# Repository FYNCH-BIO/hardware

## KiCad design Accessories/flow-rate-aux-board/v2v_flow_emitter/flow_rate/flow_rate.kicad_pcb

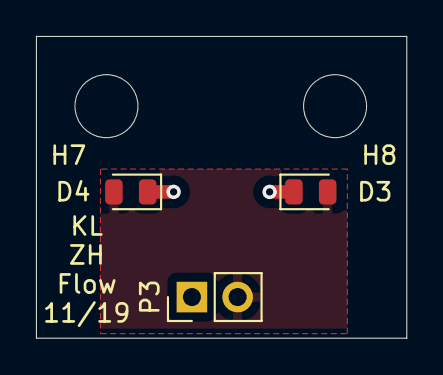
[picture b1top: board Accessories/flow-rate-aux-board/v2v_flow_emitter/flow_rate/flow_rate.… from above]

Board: 2 copper layers, 20.6 x 16.8 mm, 5 parts (0 on the bottom side), 2 nets.

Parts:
D3, D4: D; D_0805_2012Metric
H7, H8: MountingHole; MountingHole_3.5mm
P3: CONN_01X02; PinHeader_1x02_P2.54mm_Vertical

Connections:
/LED_GND: D3.1, D4.1, P3.1
/LED_PWR: D3.2, D4.2, P3.2

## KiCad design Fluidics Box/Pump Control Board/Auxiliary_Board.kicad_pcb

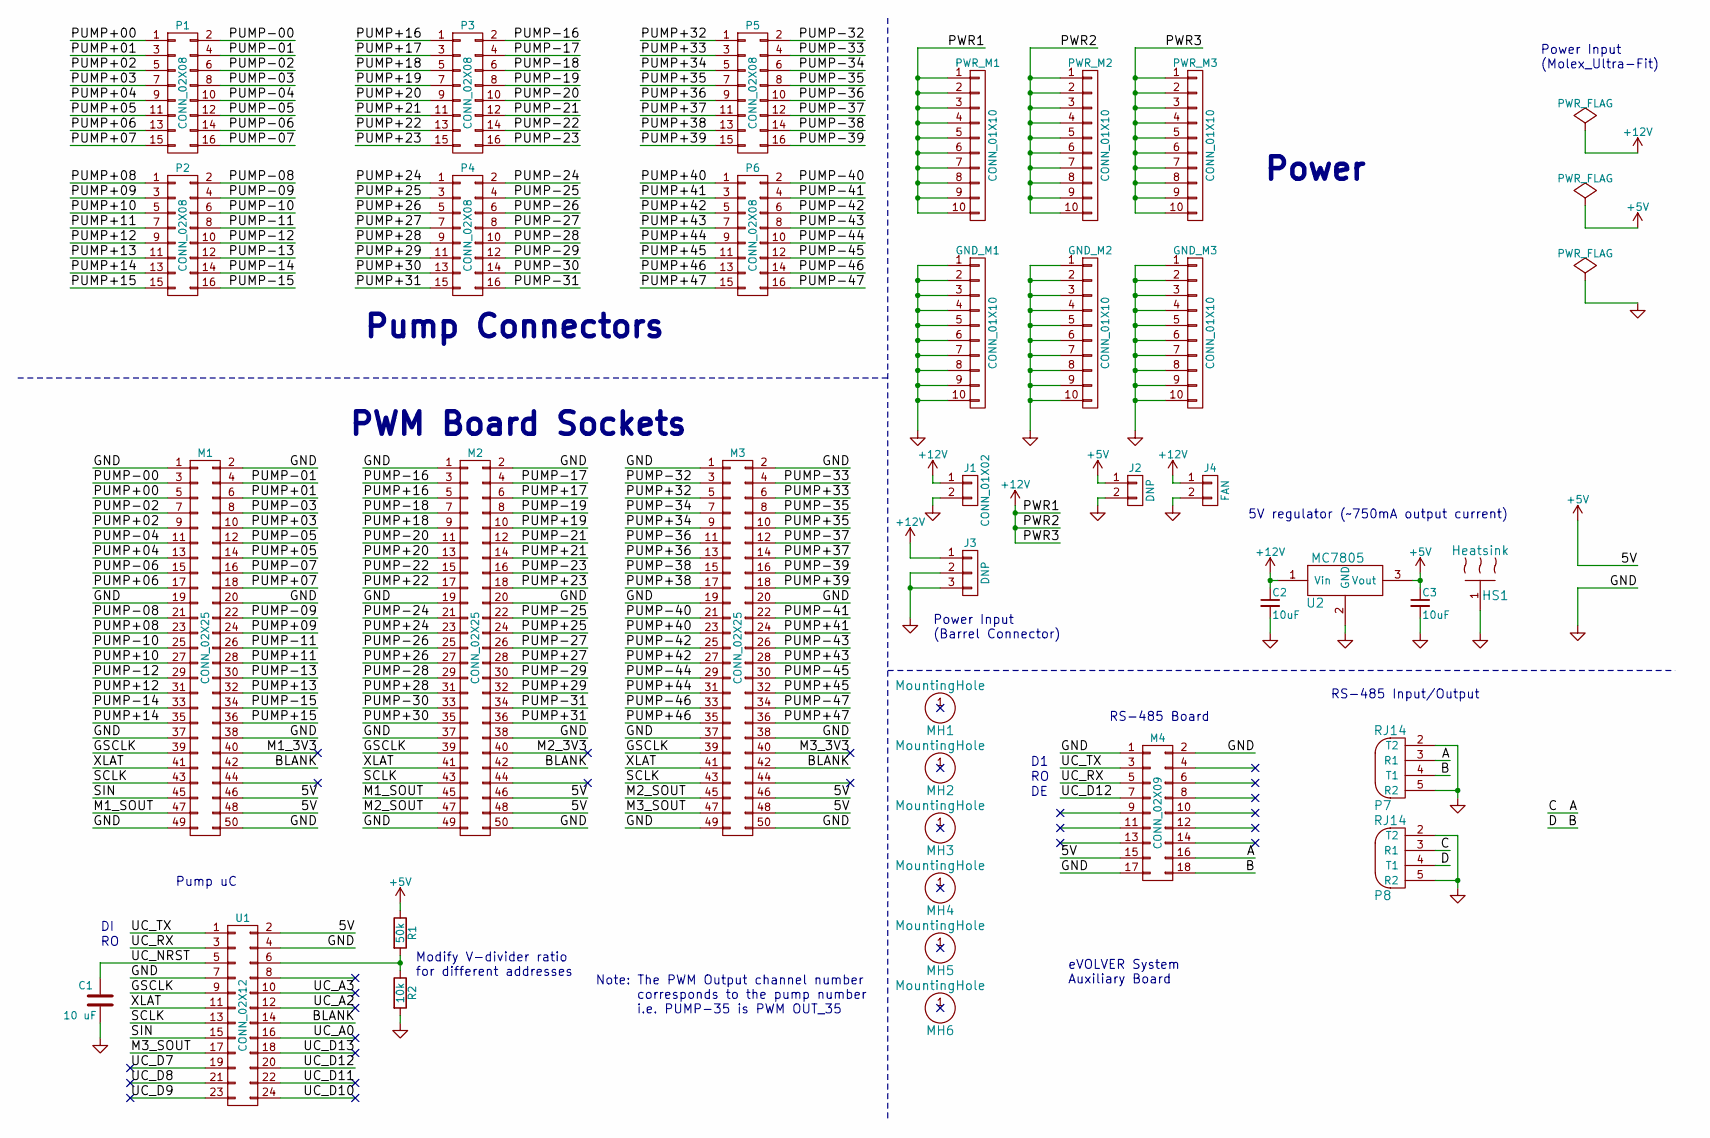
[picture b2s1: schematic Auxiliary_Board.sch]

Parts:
C1: 10 uF; FK18X5R0J105K
C2, C3: 10uF; FK18X5R0J105K
GND_M1, GND_M2, GND_M3: CONN_01X10; 10pin_tenth_in
HS1: Heatsink; CSM222-30AE
J1: CONN_01X02; OSTYK51102030
J2: DNP; OSTYK51102030
J3: DNP; 2.1mm_DC_Jack
J4: FAN; OSTYK51102030
M1, M2, M3: CONN_02X25; 50_pin_10in
M4: CONN_02X09; 2x_9_pin_10in
MH1, MH2, MH3, MH4, MH5, MH6: MountingHole; mh_632
P1, P2, P3, P4, P5, P6: CONN_02X08; 2x8_conn_10in
P7, P8: RJ14
PWR_M1, PWR_M2, PWR_M3: CONN_01X10; 10pin_tenth_in
R1: 50k; R_0.25W
R2: 10k; R_0.25W
U1: CONN_02X12; 24_pin_10in
U2: MC7805; TO-220

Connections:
+5V: C3.1, J2.1, M1.46, M1.48, M2.46, M2.48, M3.46, M3.48, M4.15, R1.1, U1.2, U2.3 (Vout)
+12V: C2.1, J1.1, J3.1, J4.1, PWR_M1.1, PWR_M1.2, PWR_M1.3, PWR_M1.4, PWR_M1.5, PWR_M1.6, PWR_M1.7, PWR_M1.8, PWR_M1.9, PWR_M1.10, PWR_M2.1, PWR_M2.2, PWR_M2.3, PWR_M2.4, PWR_M2.5, PWR_M2.6, PWR_M2.7, PWR_M2.8, PWR_M2.9, PWR_M2.10, PWR_M3.1, PWR_M3.2, PWR_M3.3, PWR_M3.4, PWR_M3.5, PWR_M3.6, PWR_M3.7, PWR_M3.8, PWR_M3.9, PWR_M3.10, U2.1 (Vin)
/A: M4.16, P7.3 (R1), P8.3 (R1)
/B: M4.18, P7.4 (T1), P8.4 (T1)
/BLANK: M1.42, M2.42, M3.42, U1.14
/GSCLK: M1.39, M2.39, M3.39, U1.9
/M1_3V3: M1.40
/M1_SOUT: M1.47, M2.45
/M2_3V3: M2.40
/M2_SOUT: M2.47, M3.45
/M3_3V3: M3.40
/M3_SOUT: M3.47, U1.17
/PUMP+00: M1.5, P1.1
/PUMP+01: M1.6, P1.3
/PUMP+02: M1.9, P1.5
/PUMP+03: M1.10, P1.7
/PUMP+04: M1.13, P1.9
/PUMP+05: M1.14, P1.11
/PUMP+06: M1.17, P1.13
/PUMP+07: M1.18, P1.15
/PUMP+08: M1.23, P2.1
/PUMP+09: M1.24, P2.3
/PUMP+10: M1.27, P2.5
/PUMP+11: M1.28, P2.7
/PUMP+12: M1.31, P2.9
/PUMP+13: M1.32, P2.11
/PUMP+14: M1.35, P2.13
/PUMP+15: M1.36, P2.15
/PUMP+16: M2.5, P3.1
/PUMP+17: M2.6, P3.3
/PUMP+18: M2.9, P3.5
/PUMP+19: M2.10, P3.7
/PUMP+20: M2.13, P3.9
/PUMP+21: M2.14, P3.11
/PUMP+22: M2.17, P3.13
/PUMP+23: M2.18, P3.15
/PUMP+24: M2.23, P4.1
/PUMP+25: M2.24, P4.3
/PUMP+26: M2.27, P4.5
/PUMP+27: M2.28, P4.7
/PUMP+28: M2.31, P4.9
/PUMP+29: M2.32, P4.11
/PUMP+30: M2.35, P4.13
/PUMP+31: M2.36, P4.15
/PUMP+32: M3.5, P5.1
/PUMP+33: M3.6, P5.3
/PUMP+34: M3.9, P5.5
/PUMP+35: M3.10, P5.7
/PUMP+36: M3.13, P5.9
/PUMP+37: M3.14, P5.11
/PUMP+38: M3.17, P5.13
/PUMP+39: M3.18, P5.15
/PUMP+40: M3.23, P6.1
/PUMP+41: M3.24, P6.3
/PUMP+42: M3.27, P6.5
/PUMP+43: M3.28, P6.7
/PUMP+44: M3.31, P6.9
/PUMP+45: M3.32, P6.11
/PUMP+46: M3.35, P6.13
/PUMP+47: M3.36, P6.15
/PUMP-00: M1.3, P1.2
/PUMP-01: M1.4, P1.4
/PUMP-02: M1.7, P1.6
/PUMP-03: M1.8, P1.8
/PUMP-04: M1.11, P1.10
/PUMP-05: M1.12, P1.12
/PUMP-06: M1.15, P1.14
/PUMP-07: M1.16, P1.16
/PUMP-08: M1.21, P2.2
/PUMP-09: M1.22, P2.4
/PUMP-10: M1.25, P2.6
/PUMP-11: M1.26, P2.8
/PUMP-12: M1.29, P2.10
/PUMP-13: M1.30, P2.12
/PUMP-14: M1.33, P2.14
/PUMP-15: M1.34, P2.16
/PUMP-16: M2.3, P3.2
/PUMP-17: M2.4, P3.4
/PUMP-18: M2.7, P3.6
/PUMP-19: M2.8, P3.8
/PUMP-20: M2.11, P3.10
/PUMP-21: M2.12, P3.12
/PUMP-22: M2.15, P3.14
/PUMP-23: M2.16, P3.16
/PUMP-24: M2.21, P4.2
/PUMP-25: M2.22, P4.4
/PUMP-26: M2.25, P4.6
/PUMP-27: M2.26, P4.8
/PUMP-28: M2.29, P4.10
/PUMP-29: M2.30, P4.12
/PUMP-30: M2.33, P4.14
/PUMP-31: M2.34, P4.16
/PUMP-32: M3.3, P5.2
/PUMP-33: M3.4, P5.4
/PUMP-34: M3.7, P5.6
/PUMP-35: M3.8, P5.8
/PUMP-36: M3.11, P5.10
/PUMP-37: M3.12, P5.12
/PUMP-38: M3.15, P5.14
/PUMP-39: M3.16, P5.16
/PUMP-40: M3.21, P6.2
/PUMP-41: M3.22, P6.4
/PUMP-42: M3.25, P6.6
/PUMP-43: M3.26, P6.8
/PUMP-44: M3.29, P6.10
/PUMP-45: M3.30, P6.12
/PUMP-46: M3.33, P6.14
/PUMP-47: M3.34, P6.16
/SCLK: M1.43, M2.43, M3.43, U1.13
/SIN: M1.45, U1.15
/UC_A0: U1.16
/UC_A2: U1.12
/UC_A3: U1.10
/UC_D7: U1.19
/UC_D8: U1.21
/UC_D9: U1.23
/UC_D10: U1.24
/UC_D11: U1.22
/UC_D12: M4.7, U1.20
/UC_D13: U1.18
/UC_NRST: C1.1, U1.5
/UC_RX: M4.5, U1.3
/UC_TX: M4.3, U1.1
/XLAT: M1.41, M2.41, M3.41, U1.11
GND: C1.2, C2.2, C3.2, GND_M1.1, GND_M1.2, GND_M1.3, GND_M1.4, GND_M1.5, GND_M1.6, GND_M1.7, GND_M1.8, GND_M1.9, GND_M1.10, GND_M2.1, GND_M2.2, GND_M2.3, GND_M2.4, GND_M2.5, GND_M2.6, GND_M2.7, GND_M2.8, GND_M2.9, GND_M2.10, GND_M3.1, GND_M3.2, GND_M3.3, GND_M3.4, GND_M3.5, GND_M3.6, GND_M3.7, GND_M3.8, GND_M3.9, GND_M3.10, HS1.1, J1.2, J2.2, J3.2, J3.3, J4.2, M1.1, M1.2, M1.19, M1.20, M1.37, M1.38, M1.49, M1.50, M2.1, M2.2, M2.19, M2.20, M2.37, M2.38, M2.49, M2.50, M3.1, M3.2, M3.19, M3.20, M3.37, M3.38, M3.49, M3.50, M4.1, M4.2, M4.17, P7.2 (T2), P7.5 (R2), P8.2 (T2), P8.5 (R2), R2.2, U1.4, U1.7, U2.2 (GND)
unnamed: R1.2, R2.1, U1.6

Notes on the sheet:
RS-485 Board
RS-485 Input/Output
Power Input (Barrel Connector)
Power Input (Molex_Ultra-Fit)
Pump uC
Pump Connectors
PWM Board Sockets
Power
Note: The PWM Output channel number corresponds to the pump number i.e. PUMP-35 is PWM OUT_35
eVOLVER System Auxiliary Board
5V regulator (~~750mA output current)
Modify V-divider ratio for different addresses

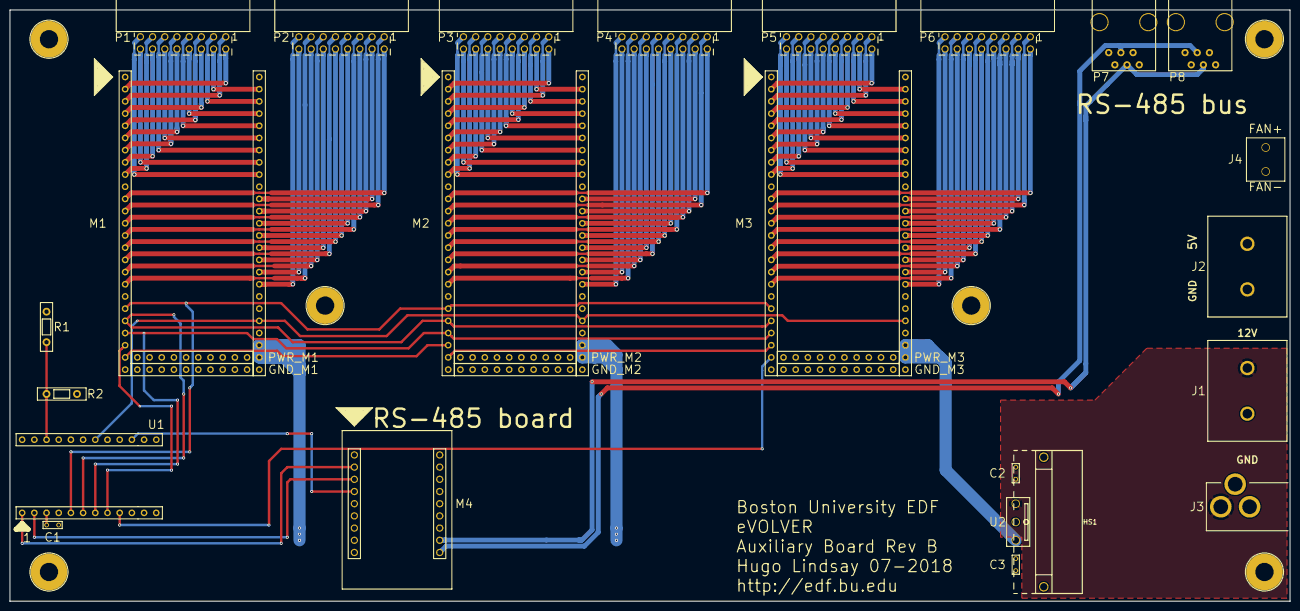
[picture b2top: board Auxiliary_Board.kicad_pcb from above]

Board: 4 copper layers, 266.7 x 123.2 mm, 36 parts (0 on the bottom side), 114 nets.

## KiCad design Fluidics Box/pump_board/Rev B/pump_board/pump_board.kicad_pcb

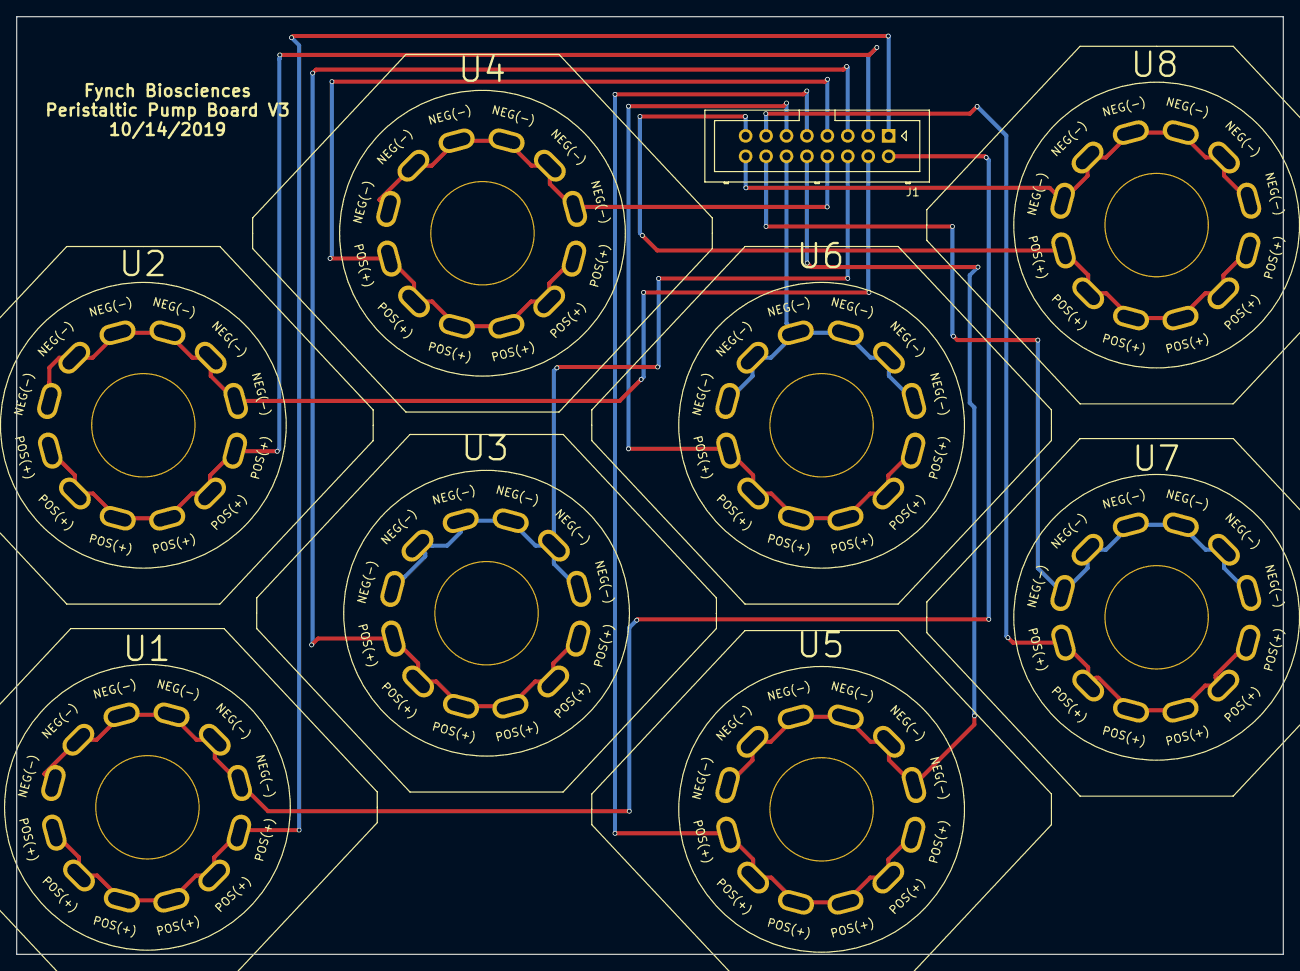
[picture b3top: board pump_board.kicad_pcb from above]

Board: 2 copper layers, 157.5 x 116.6 mm, 9 parts (0 on the bottom side), 16 nets.

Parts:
J1: Conn_02x08_Odd_Even; Multicomp_MC9A12-1634_2x08x2.54mm_Straight
U1, U2, U3, U4, U5, U6, U7, U8: peristaltic_pump; peristlatic_pump_15deg_offset

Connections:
unnamed: J1.1, U1.1
unnamed: J1.2, U1.2
unnamed: J1.3, U2.1
unnamed: J1.4, U2.2
unnamed: J1.5, U3.1
unnamed: J1.6, U3.2
unnamed: J1.7, U4.1
unnamed: J1.8, U4.2
unnamed: J1.9, U5.1
unnamed: J1.10, U5.2
unnamed: J1.11, U6.1
unnamed: J1.12, U6.2
unnamed: J1.13, U7.1
unnamed: J1.14, U7.2
unnamed: J1.15, U8.1
unnamed: J1.16, U8.2

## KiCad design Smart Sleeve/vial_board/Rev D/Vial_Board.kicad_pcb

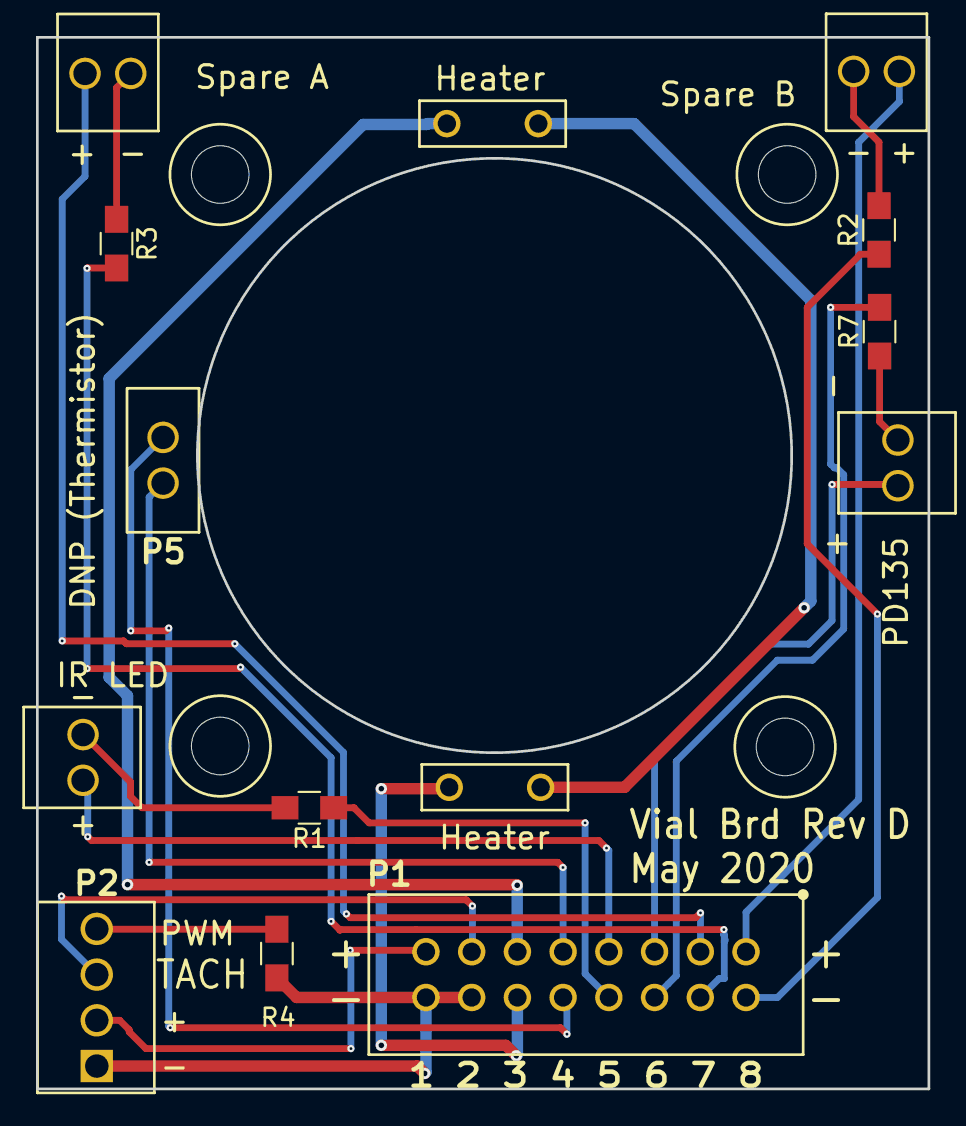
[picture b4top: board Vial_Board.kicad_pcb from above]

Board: 2 copper layers, 49.5 x 58.4 mm, 14 parts (0 on the bottom side), 21 nets.

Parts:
P1: CONN_02X08; 2x8_pin_10in
P2: CONN_01X04; 4_ScrewTerm
P5: DNP (Thermistor); Thermistor
P6: IR LED; screw_terminal
P7: PD135; screw_terminal
P8: Spare B; screw_terminal
P9: Spare A; screw_terminal
R1, R2, R3, R7: 82; R_0805_HandSoldering
R4: R; R_0805_HandSoldering
R5: Heater 1; Heater
R6: Heater 2; Heater

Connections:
/FAN+: P1.15, P2.2
/FAN-: P1.14, P1.16, P2.1, R4.2
/FS+: P1.13, P2.3
/HTR+: P1.11, R5.1
/HTR-: P1.12, R6.2
/LED+: P1.7, P6.1
/LED-: P1.8, R1.1
/PD+: P1.5, P7.1
/PD-: P1.6, R7.2
/PWM: P2.4, R4.1
/SPA+: P1.3, P9.1
/SPA-: P1.4, R3.2
/SPB+: P1.1, P8.1
/SPB-: P1.2, R2.1
/TS+: P1.9, P5.1
/TS-: P1.10, P5.2
unnamed: P6.2, R1.2
unnamed: P7.2, R7.1
unnamed: P8.2, R2.2
unnamed: P9.2, R3.1
unnamed: R5.2, R6.1

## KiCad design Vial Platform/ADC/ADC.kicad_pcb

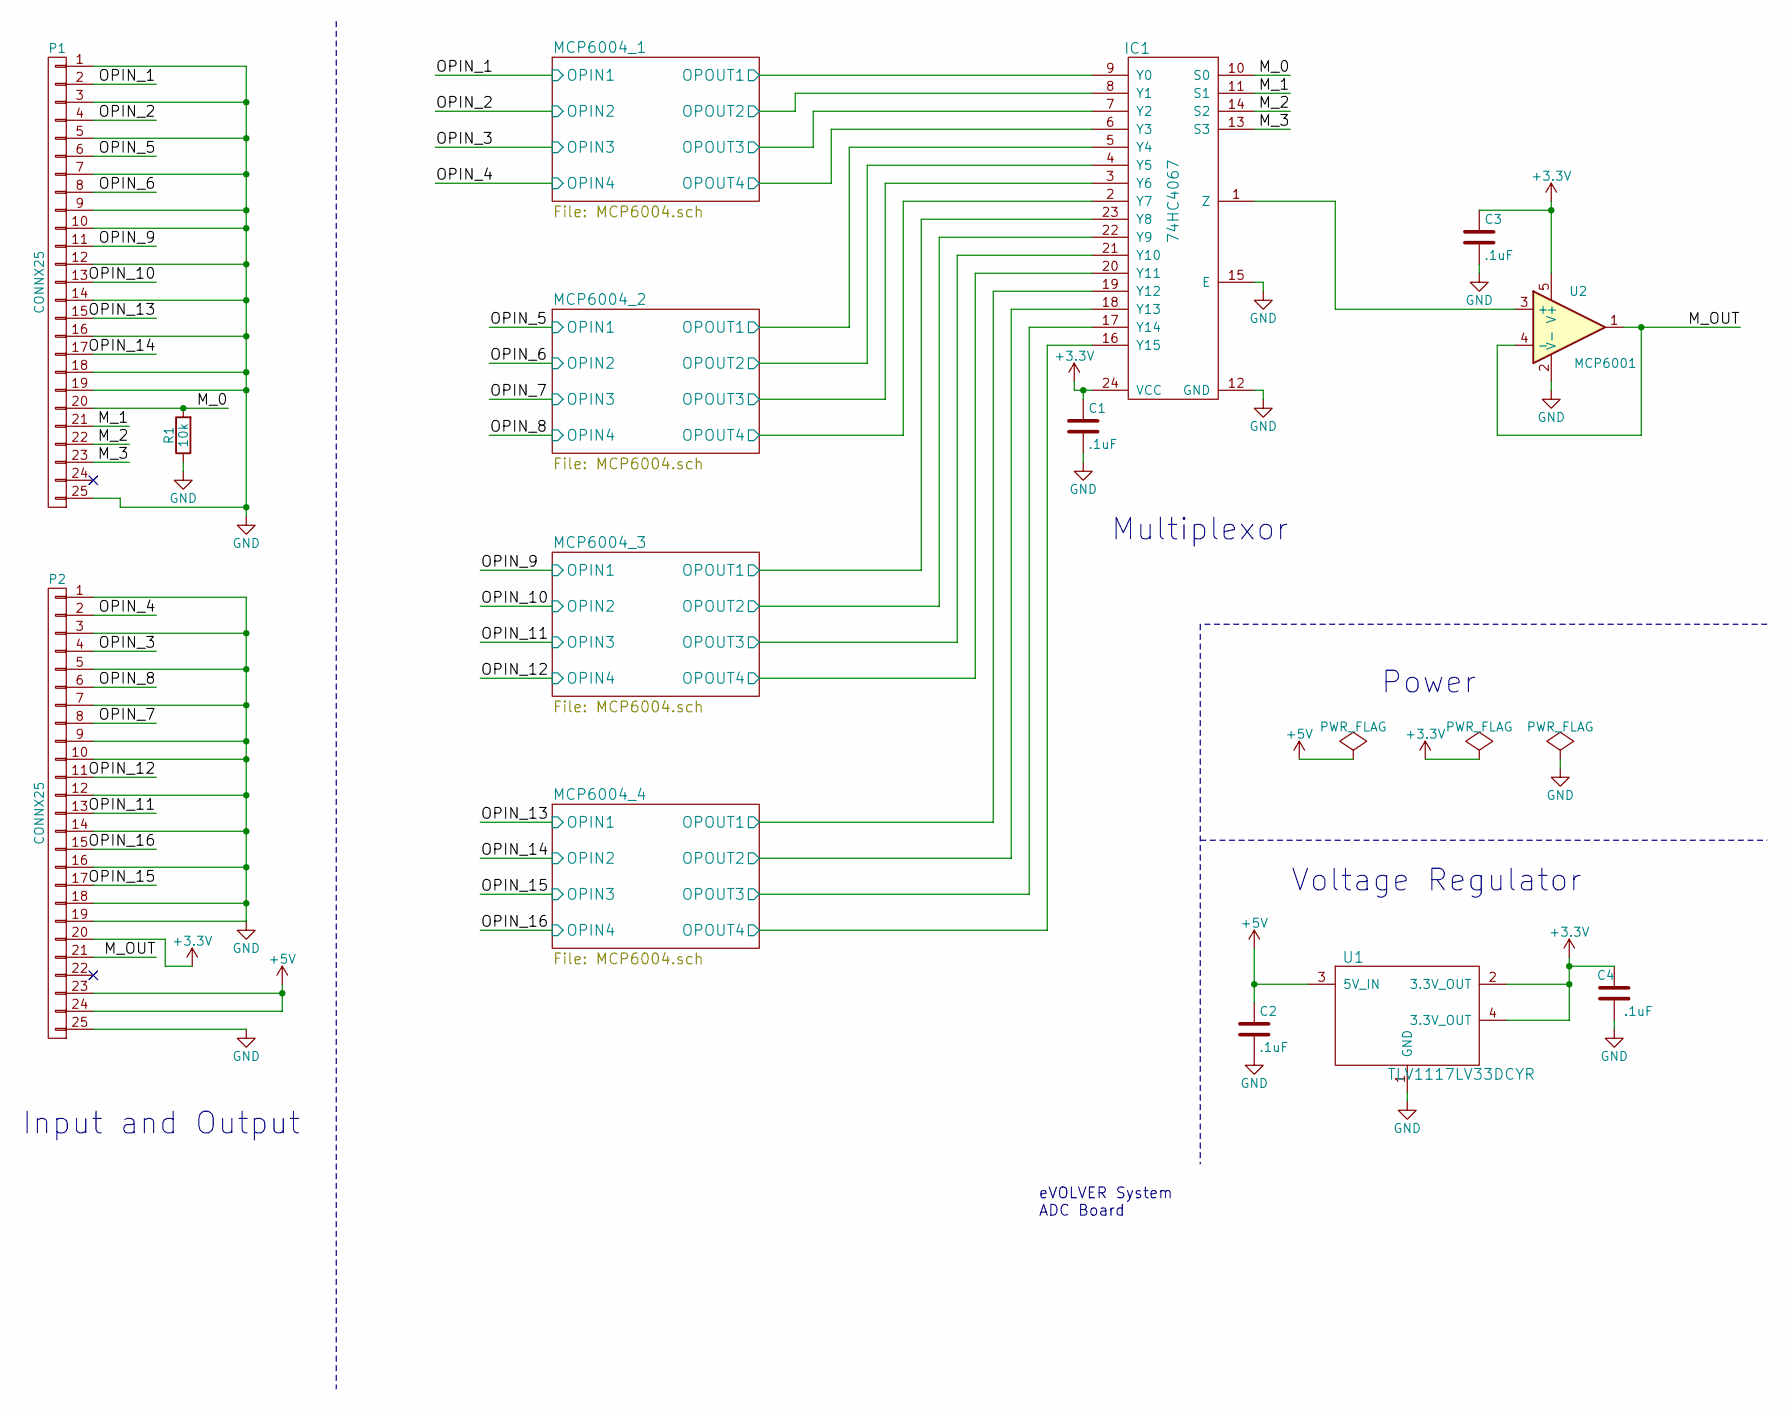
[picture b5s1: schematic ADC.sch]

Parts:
C1, C2, C3, C4: .1uF; C_0402
IC1: 74HC4067; 74HC_HTC4067
P1, P2: CONNX25; 25_pin_10in
R1: 10k; R_0402
U1: TLV1117LV33DCYR; TLV1117
U2: MCP6001

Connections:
+3V3: C1.1, C3.1, C4.1, IC1.24 (VCC), P2.20, U1.2 (3.3V_OUT), U1.4 (3.3V_OUT), U2.5 (V+); also elsewhere on the board
+5V: C2.1, P2.23, P2.24, U1.3 (5V_IN)
/MCP6004_1/OPOUT1: IC1.9 (Y0); also elsewhere on the board
/MCP6004_1/OPOUT2: IC1.8 (Y1); also elsewhere on the board
/MCP6004_1/OPOUT3: IC1.7 (Y2); also elsewhere on the board
/MCP6004_1/OPOUT4: IC1.6 (Y3); also elsewhere on the board
/MCP6004_2/OPOUT1: IC1.5 (Y4); also elsewhere on the board
/MCP6004_2/OPOUT2: IC1.4 (Y5); also elsewhere on the board
/MCP6004_2/OPOUT3: IC1.3 (Y6); also elsewhere on the board
/MCP6004_2/OPOUT4: IC1.2 (Y7); also elsewhere on the board
/MCP6004_3/OPOUT1: IC1.23 (Y8); also elsewhere on the board
/MCP6004_3/OPOUT2: IC1.22 (Y9); also elsewhere on the board
/MCP6004_3/OPOUT3: IC1.21 (Y10); also elsewhere on the board
/MCP6004_3/OPOUT4: IC1.20 (Y11); also elsewhere on the board
/MCP6004_4/OPOUT1: IC1.19 (Y12); also elsewhere on the board
/MCP6004_4/OPOUT2: IC1.18 (Y13); also elsewhere on the board
/MCP6004_4/OPOUT3: IC1.17 (Y14); also elsewhere on the board
/MCP6004_4/OPOUT4: IC1.16 (Y15); also elsewhere on the board
/M_0: IC1.10 (S0), P1.20, R1.2
/M_1: IC1.11 (S1), P1.21
/M_2: IC1.14 (S2), P1.22
/M_3: IC1.13 (S3), P1.23
/M_OUT: P2.21, U2.1, U2.4 (-)
/OPIN_1: P1.2; also elsewhere on the board
/OPIN_2: P1.4; also elsewhere on the board
/OPIN_3: P2.4; also elsewhere on the board
/OPIN_4: P2.2; also elsewhere on the board
/OPIN_5: P1.6; also elsewhere on the board
/OPIN_6: P1.8; also elsewhere on the board
/OPIN_7: P2.8; also elsewhere on the board
/OPIN_8: P2.6; also elsewhere on the board
/OPIN_9: P1.11; also elsewhere on the board
/OPIN_10: P1.13; also elsewhere on the board
/OPIN_11: P2.13; also elsewhere on the board
/OPIN_12: P2.11; also elsewhere on the board
/OPIN_13: P1.15; also elsewhere on the board
/OPIN_14: P1.17; also elsewhere on the board
/OPIN_15: P2.17; also elsewhere on the board
/OPIN_16: P2.15; also elsewhere on the board
GND: C1.2, C2.2, C3.2, C4.2, IC1.12 (GND), IC1.15 (E), P1.1, P1.3, P1.5, P1.7, P1.9, P1.10, P1.12, P1.14, P1.16, P1.18, P1.19, P1.25, P2.1, P2.3, P2.5, P2.7, P2.9, P2.10, P2.12, P2.14, P2.16, P2.18, P2.19, P2.25, R1.1, U1.1 (GND), U2.2 (V-); also elsewhere on the board
unnamed: IC1.1 (Z), U2.3 (+)

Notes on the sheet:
Input and Output
Power
Voltage Regulator
Multiplexor
eVOLVER System ADC Board

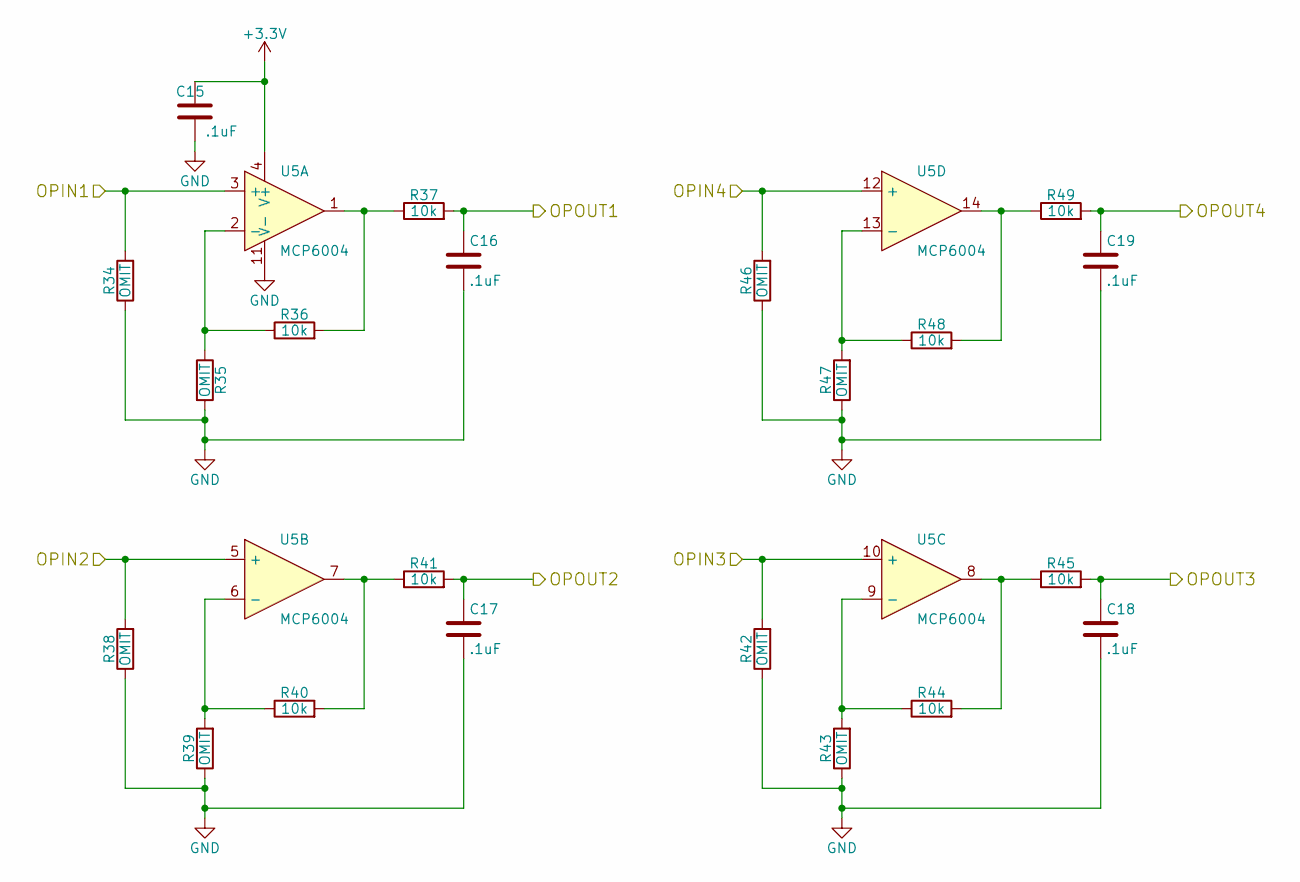
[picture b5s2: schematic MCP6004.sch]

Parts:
C5, C6, C7, C8, C9: .1uF; C_0402
R2, R3, R6, R7, R10, R11, R14, R15: OMIT; R_0402
R4, R5, R8, R9, R12, R13, R16, R17: 10k; R_0402
U3: MCP6004

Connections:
+3V3: C5.1, U3.4 (V+); also elsewhere on the board
/MCP6004_1/OPOUT1: C6.1, R5.2; also elsewhere on the board
/MCP6004_1/OPOUT2: C7.1, R9.2; also elsewhere on the board
/MCP6004_1/OPOUT3: C8.1, R13.2; also elsewhere on the board
/MCP6004_1/OPOUT4: C9.1, R17.2; also elsewhere on the board
/OPIN_1: R2.2, U3.3 (+); also elsewhere on the board
/OPIN_2: R6.2, U3.5 (+); also elsewhere on the board
/OPIN_3: R10.2, U3.10 (+); also elsewhere on the board
/OPIN_4: R14.2, U3.12 (+); also elsewhere on the board
GND: C5.2, C6.2, C7.2, C8.2, C9.2, R2.1, R3.2, R6.1, R7.1, R10.1, R11.1, R14.1, R15.1, U3.11 (V-); also elsewhere on the board
unnamed: R3.1, R4.1, U3.2 (-)
unnamed: R4.2, R5.1, U3.1
unnamed: R7.2, R8.1, U3.6 (-)
unnamed: R8.2, R9.1, U3.7
unnamed: R11.2, R12.1, U3.9 (-)
unnamed: R12.2, R13.1, U3.8
unnamed: R15.2, R16.1, U3.13 (-)
unnamed: R16.2, R17.1, U3.14

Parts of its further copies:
C10, C11, C12, C13, C14, C15, C16, C17, C18, C19, C20, C21, C22, C23, C24: .1uF; C_0402
R18, R19, R22, R23, R26, R27, R30, R31, R34, R35, R38, R39, R42, R43, R46, R47, R50, R51, R54, R55, R58, R59, R62, R63: OMIT; R_0402
R20, R21, R24, R25, R28, R29, R32, R33, R36, R37, R40, R41, R44, R45, R48, R49, R52, R53, R56, R57, R60, R61, R64, R65: 10k; R_0402
U4, U5, U6: MCP6004

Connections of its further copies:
+3V3: C10.1, C15.1, C20.1, U4.4 (V+), U5.4 (V+), U6.4 (V+); also elsewhere on the board
/MCP6004_2/OPOUT1: C11.1, R21.2; also elsewhere on the board
/MCP6004_2/OPOUT2: C12.1, R25.2; also elsewhere on the board
/MCP6004_2/OPOUT3: C13.1, R29.2; also elsewhere on the board
/MCP6004_2/OPOUT4: C14.1, R33.2; also elsewhere on the board
/MCP6004_3/OPOUT1: C16.1, R37.2; also elsewhere on the board
/MCP6004_3/OPOUT2: C17.1, R41.2; also elsewhere on the board
/MCP6004_3/OPOUT3: C18.1, R45.2; also elsewhere on the board
/MCP6004_3/OPOUT4: C19.1, R49.2; also elsewhere on the board
/MCP6004_4/OPOUT1: C21.1, R53.2; also elsewhere on the board
/MCP6004_4/OPOUT2: C22.1, R57.2; also elsewhere on the board
/MCP6004_4/OPOUT3: C23.1, R61.2; also elsewhere on the board
/MCP6004_4/OPOUT4: C24.1, R65.2; also elsewhere on the board
/OPIN_5: R18.2, U4.3 (+); also elsewhere on the board
/OPIN_6: R22.2, U4.5 (+); also elsewhere on the board
/OPIN_7: R26.2, U4.10 (+); also elsewhere on the board
/OPIN_8: R30.2, U4.12 (+); also elsewhere on the board
/OPIN_9: R34.2, U5.3 (+); also elsewhere on the board
/OPIN_10: R38.2, U5.5 (+); also elsewhere on the board
/OPIN_11: R42.2, U5.10 (+); also elsewhere on the board
/OPIN_12: R46.2, U5.12 (+); also elsewhere on the board
/OPIN_13: R50.2, U6.3 (+); also elsewhere on the board
/OPIN_14: R54.2, U6.5 (+); also elsewhere on the board
/OPIN_15: R58.2, U6.10 (+); also elsewhere on the board
/OPIN_16: R62.2, U6.12 (+); also elsewhere on the board
GND: C10.2, C11.2, C12.2, C13.2, C14.2, C15.2, C16.2, C17.2, C18.2, C19.2, C20.2, C21.2, C22.2, C23.2, C24.2, R18.1, R19.2, R22.1, R23.1, R26.1, R27.1, R30.1, R31.1, R34.1, R35.2, R38.1, R39.1, R42.1, R43.1, R46.1, R47.1, R50.1, R51.2, R54.1, R55.1, R58.1, R59.1, R62.1, R63.1, U4.11 (V-), U5.11 (V-), U6.11 (V-); also elsewhere on the board
unnamed: R19.1, R20.1, U4.2 (-)
unnamed: R20.2, R21.1, U4.1
unnamed: R23.2, R24.1, U4.6 (-)
unnamed: R24.2, R25.1, U4.7
unnamed: R27.2, R28.1, U4.9 (-)
unnamed: R28.2, R29.1, U4.8
unnamed: R31.2, R32.1, U4.13 (-)
unnamed: R32.2, R33.1, U4.14
unnamed: R35.1, R36.1, U5.2 (-)
unnamed: R36.2, R37.1, U5.1
unnamed: R39.2, R40.1, U5.6 (-)
unnamed: R40.2, R41.1, U5.7
unnamed: R43.2, R44.1, U5.9 (-)
unnamed: R44.2, R45.1, U5.8
unnamed: R47.2, R48.1, U5.13 (-)
unnamed: R48.2, R49.1, U5.14
unnamed: R51.1, R52.1, U6.2 (-)
unnamed: R52.2, R53.1, U6.1
unnamed: R55.2, R56.1, U6.6 (-)
unnamed: R56.2, R57.1, U6.7
unnamed: R59.2, R60.1, U6.9 (-)
unnamed: R60.2, R61.1, U6.8
unnamed: R63.2, R64.1, U6.13 (-)
unnamed: R64.2, R65.1, U6.14

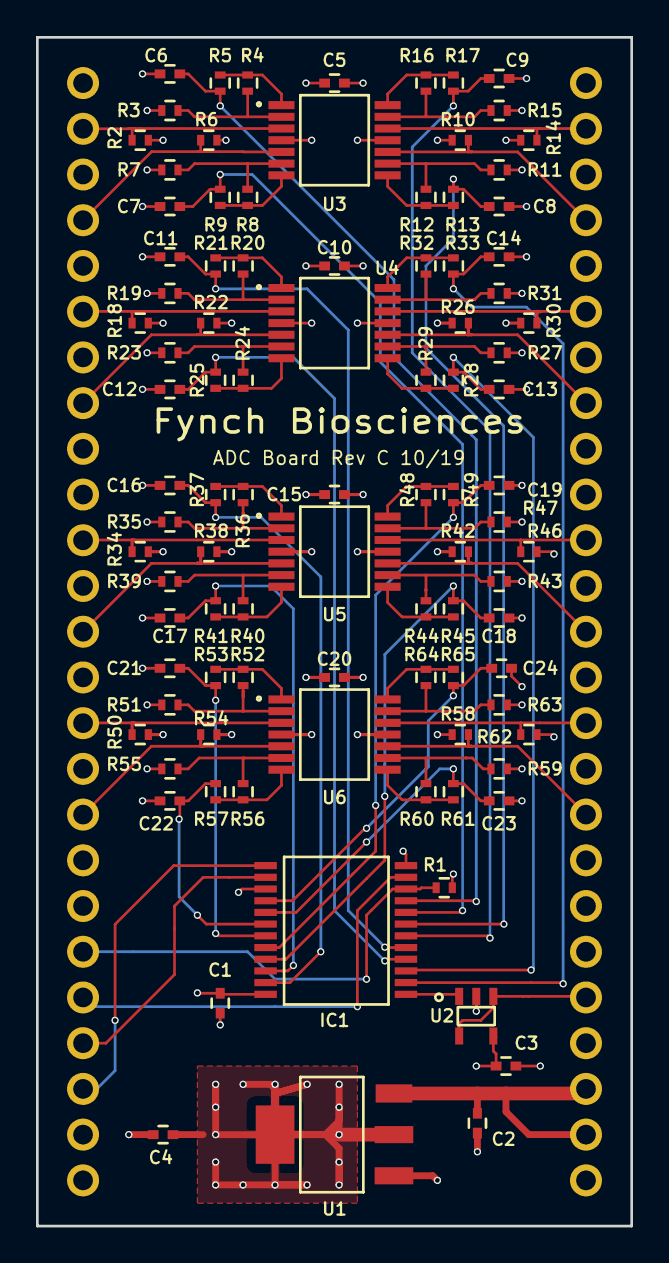
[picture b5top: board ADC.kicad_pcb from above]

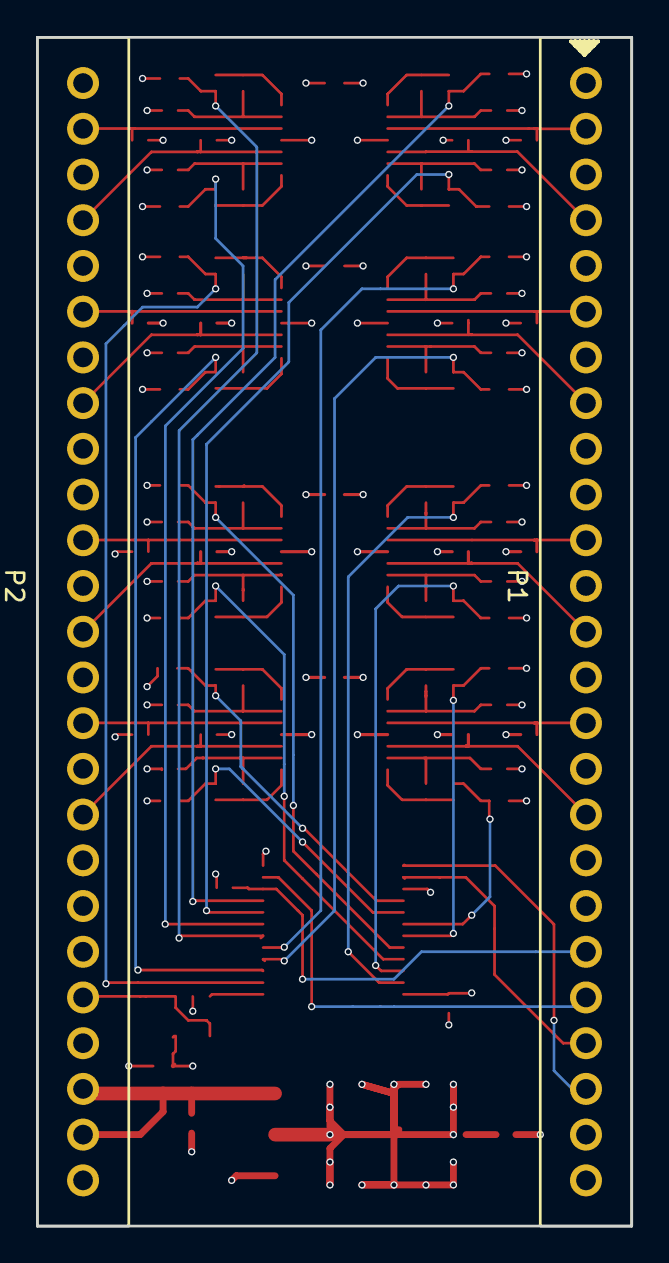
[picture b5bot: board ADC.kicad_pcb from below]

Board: 4 copper layers, 33.0 x 66.0 mm, 98 parts (2 on the bottom side), 73 nets.

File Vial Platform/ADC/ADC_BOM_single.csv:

Reference, Value, Footprint, Datasheet, Supplier Num, Supplier Name
"U1","TLV1117LV33DCYR","ADC:TLV1117","","296-28778-1-ND","Texas Instruments","
",""
"C4",".1uF","Capacitors_SMD:C_0402","","",""
"C2",".1uF","Capacitors_SMD:C_0402","","",""
"P1","CONNX25","mods:25_pin_10in","","ED10025-ND","Mill-Max Manufacturing Corp.","
",""
"P2","CONNX25","mods:25_pin_10in","","ED10025-ND","Mill-Max Manufacturing Corp.","
",""
"IC1","74HC4067","ADC:74HC_HTC4067","","568-12173-2-ND","NXP Semiconductors","
",""
"C1",".1uF","Capacitors_SMD:C_0402","","",""
"C3",".1uF","Capacitors_SMD:C_0402","","",""
"U2","MCP6001","ADC:MCP6001","","MCP6001T-I/OTCT-ND","Microchip Technology","
",""
"R1","10k","Resistors_SMD:R_0402","","",""
"U3","MCP6004","ADC:MCP6004","","MCP6004T-I/STCT-ND","Microchip Technology","
",""
"R2","1 M ","Resistors_SMD:R_0402","","",""
"R4","R","Resistors_SMD:R_0402","","",""
"R3","R","Resistors_SMD:R_0402","","",""
"R5","10k","Resistors_SMD:R_0402","","",""
"C5",".1uF","Capacitors_SMD:C_0402","","",""
"R10","1 M ","Resistors_SMD:R_0402","","",""
"R11","R","Resistors_SMD:R_0402","","",""
"R12","R","Resistors_SMD:R_0402","","",""
"R13","10k","Resistors_SMD:R_0402","","",""
"R14","1 M ","Resistors_SMD:R_0402","","",""
"R15","R","Resistors_SMD:R_0402","","",""
"R16","R","Resistors_SMD:R_0402","","",""
"R17","10k","Resistors_SMD:R_0402","","",""
"R6","1 M ","Resistors_SMD:R_0402","","",""
"R7","R","Resistors_SMD:R_0402","","",""
"R8","R","Resistors_SMD:R_0402","","",""
"R9","10k","Resistors_SMD:R_0402","","",""
"C6",".1uF","Capacitors_SMD:C_0402","","",""
"C8",".1uF","Capacitors_SMD:C_0402","","",""
"C7",".1uF","Capacitors_SMD:C_0402","","",""
"C9",".1uF","Capacitors_SMD:C_0402","","",""
"U4","MCP6004","ADC:MCP6004","","MCP6004T-I/STCT-ND","Microchip Technology","
",""
"R18","1 M ","Resistors_SMD:R_0402","","",""
"R20","R","Resistors_SMD:R_0402","","",""
"R19","R","Resistors_SMD:R_0402","","",""
"R21","10k","Resistors_SMD:R_0402","","",""
"C10",".1uF","Capacitors_SMD:C_0402","","",""
"R26","1 M ","Resistors_SMD:R_0402","","",""
"R27","R","Resistors_SMD:R_0402","","",""
"R28","R","Resistors_SMD:R_0402","","",""
"R29","10k","Resistors_SMD:R_0402","","",""
"R30","1 M ","Resistors_SMD:R_0402","","",""
"R31","R","Resistors_SMD:R_0402","","",""
"R32","R","Resistors_SMD:R_0402","","",""
"R33","10k","Resistors_SMD:R_0402","","",""
"R22","1 M ","Resistors_SMD:R_0402","","",""
"R23","R","Resistors_SMD:R_0402","","",""
"R24","R","Resistors_SMD:R_0402","","",""
"R25","10k","Resistors_SMD:R_0402","","",""
"C11",".1uF","Capacitors_SMD:C_0402","","",""
"C13",".1uF","Capacitors_SMD:C_0402","","",""
"C12",".1uF","Capacitors_SMD:C_0402","","",""
"C14",".1uF","Capacitors_SMD:C_0402","","",""
"U5","MCP6004","ADC:MCP6004","","MCP6004T-I/STCT-ND","Microchip Technology","
",""
"R34","1 M ","Resistors_SMD:R_0402","","",""
"R36","R","Resistors_SMD:R_0402","","",""
"R35","R","Resistors_SMD:R_0402","","",""
"R37","10k","Resistors_SMD:R_0402","","",""
"C15",".1uF","Capacitors_SMD:C_0402","","",""
"R42","1 M ","Resistors_SMD:R_0402","","",""
"R43","R","Resistors_SMD:R_0402","","",""
"R44","R","Resistors_SMD:R_0402","","",""
"R45","10k","Resistors_SMD:R_0402","","",""
"R46","1 M ","Resistors_SMD:R_0402","","",""
"R47","R","Resistors_SMD:R_0402","","",""
"R48","R","Resistors_SMD:R_0402","","",""
"R49","10k","Resistors_SMD:R_0402","","",""
"R38","1 M ","Resistors_SMD:R_0402","","",""
"R39","R","Resistors_SMD:R_0402","","",""
"R40","R","Resistors_SMD:R_0402","","",""
"R41","10k","Resistors_SMD:R_0402","","",""
"C16",".1uF","Capacitors_SMD:C_0402","","",""
"C18",".1uF","Capacitors_SMD:C_0402","","",""
"C17",".1uF","Capacitors_SMD:C_0402","","",""
"C19",".1uF","Capacitors_SMD:C_0402","","",""
"U6","MCP6004","ADC:MCP6004","","MCP6004T-I/STCT-ND","Microchip Technology","
",""
"R50","1 M ","Resistors_SMD:R_0402","","",""
"R52","R","Resistors_SMD:R_0402","","",""
"R51","R","Resistors_SMD:R_0402","","",""
"R53","10k","Resistors_SMD:R_0402","","",""
"C20",".1uF","Capacitors_SMD:C_0402","","",""
"R58","1 M ","Resistors_SMD:R_0402","","",""
"R59","R","Resistors_SMD:R_0402","","",""
"R60","R","Resistors_SMD:R_0402","","",""
"R61","10k","Resistors_SMD:R_0402","","",""
"R62","1 M ","Resistors_SMD:R_0402","","",""
"R63","R","Resistors_SMD:R_0402","","",""
"R64","R","Resistors_SMD:R_0402","","",""
"R65","10k","Resistors_SMD:R_0402","","",""
"R54","1 M ","Resistors_SMD:R_0402","","",""
"R55","R","Resistors_SMD:R_0402","","",""
"R56","R","Resistors_SMD:R_0402","","",""
"R57","10k","Resistors_SMD:R_0402","","",""
"C21",".1uF","Capacitors_SMD:C_0402","","",""
"C23",".1uF","Capacitors_SMD:C_0402","","",""
"C22",".1uF","Capacitors_SMD:C_0402","","",""
"C24",".1uF","Capacitors_SMD:C_0402","","",""
